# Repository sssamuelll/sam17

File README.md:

<h1 align="center">SAM17</h1>

<p align="center"><strong>A 16-voice analog synthesizer that patches like a modular and recalls like a polysynth.</strong></p>

<p align="center">
  16 complete analog voices &nbsp;·&nbsp; FM matrix 16×16 &nbsp;·&nbsp; 8-in/8-out patch bay &nbsp;·&nbsp; STM32N657 brain running Rust &nbsp;·&nbsp; three rows on Eurorack rails<br>
  hardware CERN-OHL-S v2 &nbsp;·&nbsp; firmware GPL-3.0-or-later &nbsp;·&nbsp; documentation CC BY-SA 4.0
</p>

<p align="center">
  <a href="docs/superpowers/specs">Specs</a> &nbsp;·&nbsp;
  <a href="hardware">Hardware</a> &nbsp;·&nbsp;
  <a href="software/nucleo">Firmware</a> &nbsp;·&nbsp;
  <a href="case">Case</a> &nbsp;·&nbsp;
  <a href="https://github.com/sssamuelll/sam17/milestones">Milestones</a>
</p>

> [!IMPORTANT]
> **There is no finished unit yet.** The render above is the console as it
> stands in the OpenSCAD model in [`case/`](case); nothing in it exists yet.
> What exists physically today, of this design, is the STM32N657 evaluation
> board on the bench, with the firmware running on it. The voice board is
> specified but not yet drawn. The power supply board is routed and its parts
> are signed, but it is not yet cleared for fabrication. The first complete
> instrument is due in May 2027. Details, with dates, under
> [Status](#status-october-2026).

It began as Samuel Ballesteros's electronic engineering thesis at Universidad
Yacambú, Venezuela, in 2020, a monophonic modular in seven modules. In 2022 the
Goethe-Institut Venezuela selected it for its programme *Pensar la Música
Electrónica en Venezuela*. Since then it has been redesigned, in Germany, as
the sixteen-voice instrument this repository describes.

The working language of the project is Spanish: specs, budgets and design
notes are written in Spanish. This README is in English because it is the
front door.

## The instrument

```mermaid
flowchart LR
  MIDI["MIDI<br/>USB and DIN"] --> C
  P["Panel and display"] --> C
  C["Brain<br/>STM32N657, Rust"] -- "J2 link (SPI)" --> V
  subgraph V["Voice module: 16 channels on one board"]
    direction LR
    O["16× SSI2130<br/>oscillators"] --> F["16× MS-20 style filter<br/>LM13700"] --> A["32× VCA<br/>SSI2164"]
    M["FM matrix 16×16"] -.-> O
    X["Crosspoint<br/>2× AD75019"] --- O
    X --- A
  end
  B["Patch bay<br/>8 inputs + 8 outputs"] --- X
  A --> S["Stereo output"]
```

*Inside the instrument the patch is a preset; outside, it is a cable.*

- Sixteen complete voices, each one oscillator → filter → VCA soldered end to
  end on the same board. The copper builds channels; **the preset assigns the
  roles**: sixteen clean voices, eight FM voices with carrier and modulator, or
  any mix.
- Sixteen rather than eight because in FM each voice needs two oscillators:
  the modulator has to track its carrier in frequency. One modulator shared by
  eight different notes gives dissonant bells.
- The oscillators are SSI2130, with saw, triangle, pulse, and sine from the
  chip's shaper. A 16-line FM matrix lets any oscillator modulate any other,
  which is why all sixteen sit in one module. Split in two, the matrix splits
  with them.
- One filter per voice, a 24 dB/oct MS-20 style low-pass on an LM13700 and a
  TL074. The resonance is controlled by a VCA, never by a digipot.
- Two VCAs per voice, signal and resonance. Thirty-two in all, on eight
  SSI2164.
- The envelopes run as code on the voice module's microcontroller, with their
  own knobs on the panel. There is no envelope circuit.
- The patch bay has eight inputs and eight outputs, with jack sensing and an
  LED per jack, routed through two AD75019, a 16×16 crosspoint. The brain sends
  the crosspoint image over the J2 link.
- The brain is an STM32N657 running bare-metal Rust
  ([`software/nucleo`](software/nucleo)). It takes MIDI over USB and DIN,
  drives the panel and the display, and talks to the voice module over the J2,
  an SPI link with its header, master and recovery already specified.
- The output is stereo, with a place for each voice in the stereo field.
- The console has three rows on 104 HP Eurorack rails. The instrument's
  unified panel is on top, 3U. A slim 55 mm utility row in the middle takes the
  instrument's connection tiles; it is not Intellijel 1U and is not advertised
  as compatible. A 3U Eurorack row below is for the instrument's own expansion
  modules, with its own current budget. The skeleton is machined aluminium.
  Each side is a louvre of black anodised aluminium, 44 vertical bars the
  instrument breathes through; the rear panel is amber, and the case stands
  on a 3 mm sheet-metal base. Dimensions, materials and drawings in
  [`case/README.md`](case/README.md).
- Power is 230 VAC through an external 24 V brick, an SL Power TE90 that
  plugs into a 4-pin mini-DIN socket on the case. In the v5 supply, signed
  on 8 September 2026 ([spec](docs/superpowers/specs/2026-09-05-fuente-v5-ladrillo-design.md)),
  the AC-DC stage moves out of the case. Inside it stay five isolated DC-DC
  modules and the cascade of linear regulators carried over from v4, behind a
  protection chain against reverse polarity, overvoltage and overload. The v5
  board is routed on four layers with a clean DRC
  ([`hardware/01-power-supply/v5/fab`](hardware/01-power-supply/v5/fab)), and
  its [parts](docs/superpowers/specs/2026-10-22-fuente-v5-piezas-propuesta.md)
  were reviewed on 25 October and signed on 26 and 27 October
  ([review](docs/superpowers/specs/2026-10-25-junta-fuente-v5-piezas.md)). It
  is not cleared for copper yet: the open questions in §9.2 of the spec, 13 of
  the original 16 after Advanced Energy's first reply on 28 October, are the
  condition for fabrication, several of them answered only by the
  manufacturers. Ten hold up the board, and three only the rear panel, the
  chassis and the display. Tests that need the built board run in its
  bring-up. The test kit runs from a bench supply.

*At night, with a light inside for the render. Each side is a louvre of 44
bars, and it is where the instrument breathes.*

## Status, October 2026

The project map is the
[GitHub milestones](https://github.com/sssamuelll/sam17/milestones):
eight stages, each with its "done when" in the description, and every issue
hangs from one of them. As of 30 October 2026:

| Milestone | Done when | Where it stands |
|---|---|---|
| 1 · Power supply v4: paper closed | No open decision is left in the power supply paper | The supply that gets built is now v5, signed on 8 September. Its parts were signed on 26 and 27 October and the board regenerated with them; its gates and DRC pass. Advanced Energy answered the first round of questions on 28 October (closing `H-V2-AISLAMIENTO`); between the board and copper stand 10 open questions of §9.2 (plus 3 outside the board), the follow-ups with Advanced Energy and TRACO Power, and three open issues. The bench tests come after, on the first board |
| 2 · Power supply v4 in copper | The supply boards are built and measured on the bench | Not started. The v5 bring-up is written as a checked sheet of 109 measurements with their limits ([`check_bringup.py`](hardware/01-power-supply/v5/check_bringup.py)) |
| 3 · The brain boots | Our firmware runs on the N657, speaks USB MIDI and lights the display | In progress: the firmware has run on the NUCLEO-N657X0-Q since 1 October. It takes USB MIDI, measured at 5,000 messages per second on 19 October, and drives the J2 link from an 8 kHz tick. After a 24-hour run at 1 kHz on 17 October, the 8 kHz soak from a Raspberry Pi finished 144 hours on 27 October (4,147,199,999 transfers with zero missed deadlines, zero late EOTs and zero bad edges, covering the 8-hour horizon) |
| 4 · Test kit: brain plus one voice | A MIDI note comes in and one voice sounds through the J2 | The current front: the J2 header and master are on paper and in the firmware, which since 20 October also carries the voice module's v1 message set. The full voice board has no KiCad in the repository yet |
| 5 · The remaining boards | The rest of the boards are in KiCad with their gates green | Pending |
| 6 · Case and panel to the workshop | Case and panel cut and assembled, with the supply inside and breathing | Skeleton drawings in [`case/plans`](case/plans). The finish was decided on 11 and 12 October: louvred sides, amber rear, sheet-metal base. Next come a sample strip of the louvre and a bench test of the 24 V socket before its floor bracket goes out for quotes ([`case/RFQ.md`](case/RFQ.md)) |
| 7 · The first SAM17 that sounds | Everything in the case, calibrated, thirty minutes without drifting | Depends on all of the above |
| 8 · Parked: does not block sound | App and plugin, sequencer, the agent | Resumes after 7 |

What exists physically today, of this design, is the N657 evaluation board on
the bench.

## Where it comes from

- [`docs/thesis.pdf`](docs/thesis.pdf): the 2020 thesis, in Spanish. Seven
  monophonic modules with three CEM3340, an MS-20 style filter, and MIDI/CV
  control from a Raspberry Pi and an AD5686R DAC. Summary in
  [`docs/summary.md`](docs/summary.md), monophonic architecture in
  [`docs/architecture.md`](docs/architecture.md).
- The v1 firmware, Python on a Raspberry Pi, stays in
  [`software/midi-cv`](software/midi-cv) for reference. It is superseded.
- The thesis numbering of seven modules survives as the folder index in
  [`hardware/`](hardware), although the current design is no longer seven
  boards: the voice module absorbed four of them, for the reason given in §1
  of the [voice module spec](docs/superpowers/specs/2026-08-23-modulo-voz-total-design.md).

## Repository map

```
sam17/
├── docs/
│   ├── superpowers/specs/   The current design: dated specs, the newest one rules.
│   ├── superpowers/plans/   Work plans, one per spec.
│   ├── modules/             Documentation per thesis module.
│   ├── reference/           Datasheets and references.
│   ├── thesis.pdf           The 2020 thesis; its summary in summary.md.
│   └── architecture*.md     Monophonic (thesis), polyphonic and compute architecture.
├── hardware/
│   ├── 01-power-supply/     Power supply: v1 to v5, bring-up and budgets; v5 is the one built.
│   ├── 02-midi-cv/          The brain: the N657 board and the J2 budgets.
│   ├── 03-vco/              The voice: 16 channels, FM matrix and patch bay (its 4-VCO v1, superseded).
│   ├── 04..07/              Mixer, VCF, ADSR and VCA from the thesis, dissolved into the voice.
│   ├── bus-board/           ±12 V distribution and the ground budget.
│   └── tools/               gates.py and the check_* and *_budget scripts that are the quality gates.
├── software/
│   ├── nucleo/              Rust firmware for the STM32N657.
│   └── midi-cv/             Python firmware of v1, superseded.
├── simulations/             SPICE per block: vco, vcf, vca, adsr, mixer, power.
├── case/                    The console: cad/ (OpenSCAD), plans/ (DXF), panels/, renders/,
│                            clearance_budget.py and the workshop PLIEGO.
├── .specify/memory/         The project constitution.
└── .githooks/               The gates that run on every push.
```

## Getting started

1. **The current design lives in the dated specs** in
   [`docs/superpowers/specs/`](docs/superpowers/specs), and the newest one
   rules. The ones governing the instrument today:
   [the voice module](docs/superpowers/specs/2026-08-23-modulo-voz-total-design.md),
   [the brain v2](docs/superpowers/specs/2026-08-21-modulo-2-v2-cerebro-design.md),
   [the whole instrument](docs/superpowers/specs/2026-09-03-instrumento-entero-design.md),
   [the power supply v5](docs/superpowers/specs/2026-09-05-fuente-v5-ladrillo-design.md),
   and for the link between brain and voice the J2
   [header](docs/superpowers/specs/2026-09-02-cabecera-j2-design.md) and
   [master](docs/superpowers/specs/2026-09-03-maestro-j2-recuperacion-design.md).
   [`docs/architecture-poly.md`](docs/architecture-poly.md) is pending a
   rewrite against them and carries a notice.
2. **The hardware quality gates** run on the Python standard library, with no
   dependencies:

   ```bash
   python hardware/tools/gates.py
   ```

   It runs every `check_*.py`, every `*_budget.py`, the simulations and the
   connectivity signature. Details in
   [`hardware/tools/README.md`](hardware/tools/README.md).
3. **The firmware:**

   ```bash
   cd software/nucleo && cargo test --workspace
   ```

   The N657 binary links separately, in `software/nucleo/fw`.
4. **The console** is regenerated from [`case/`](case): its README explains
   the OpenSCAD, the DXF and the clearance budgets.
5. **To contribute**, read the [constitution](.specify/memory/constitution.md)
   and [`CONTRIBUTING.md`](CONTRIBUTING.md). Every issue carries a milestone.

## Licence and name

See [`LICENSE`](LICENSE). Hardware designs are licensed under CERN-OHL-S v2,
software under GPL-3.0-or-later, and documentation under CC BY-SA 4.0. The
original thesis is included for documentation only.

The name **SAM17** is not part of any of the licences: you may build, modify
and sell derivatives of this design under their terms, but you may not call
them SAM17 or present them as original or endorsed units. Descriptive use
("based on the SAM17 design") is fine.

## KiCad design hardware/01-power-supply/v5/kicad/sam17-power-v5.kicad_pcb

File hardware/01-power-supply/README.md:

# Hardware — Módulo 1: Alimentación

> Documentación funcional: [`docs/modules/01-power-supply.md`](../../docs/modules/01-power-supply.md).

> **Estado (2026-10-30): la fuente que se construye es la v5.** Esta carpeta
> raíz es la v1, y todo lo que sigue debajo del banner la describe a ella.
>
> | Versión | Qué es | Estado |
> |---|---|---|
> | v1 (esta carpeta) | trafo de 12 VAC y 7805/7812/7912 | no se construye (2026-08-17); `notes/design-notes.md` es la base de la que heredan las demás |
> | [v2](v2/) | la primera cascada: pre-reguladores y LT3045/LT3094 | gerbers, BOM y CPL generados, nunca se pidió |
> | [v3](v3/) | toroide y cascada lineal | no se pide (2026-09-04); su cascada sigue valiendo |
> | [v4](v4/) | seis Mean Well IRM dentro de la caja, con la cascada | superada por la v5; sus curvas y puertas son la referencia de la cascada |
> | [v5](v5/) | ladrillo externo de 24 V; dentro, la conversión DC-DC y la cascada | D-V1..D-V5 firmadas el 2026-09-08 ([spec](../../docs/superpowers/specs/2026-09-05-fuente-v5-ladrillo-design.md)) |
>
> La placa de la v5 está ruteada en 4 capas con el DRC en cero
> ([`v5/fab/`](v5/fab/README.md)) y sus
> [piezas](../../docs/superpowers/specs/2026-10-22-fuente-v5-piezas-propuesta.md)
> quedaron firmadas el 26 y 27 de octubre
> ([junta](../../docs/superpowers/specs/2026-10-25-junta-fuente-v5-piezas.md)).
> Todavía no autoriza cobre: de los 16 HUECOS de su §9.2 quedan 13 abiertos tras
> la primera respuesta de Advanced Energy del 28 de octubre (10 bloquean la
> placa y 3 solo el panel trasero, el chasis y la pantalla). El bring-up es la
> hoja de 109 puntos de [`v5/check_bringup.py`](v5/check_bringup.py).

## Resumen

Convierte 12 VAC del transformador externo en **+5 V**, **+12 V** y **−12 V**
regulados que distribuye al resto del sintetizador a través del bus interno.

> **Variante Europa (230 VAC / 50 Hz).** La tesis original (§1 de
> [`notes/design-notes.md`](notes/design-notes.md)) asume la red eléctrica de
> Venezuela (110 VAC / 60 Hz); esta build cambia el objetivo a mains europeo
> — ver [`notes/design-notes.md` §12](notes/design-notes.md#12-variante-europa-230-vac--50-hz)
> para qué cambió (MOV, fusible, transformador) y qué se mantuvo igual (NTC,
> verificado contra datasheet).

## Componentes principales

| Función | Componente |
|---------|------------|
| Rectificación | Puente de diodos (4 × 1N4007 o equivalente) |
| Regulador +5 V | LM7805 |
| Regulador +12 V | LM7812 |
| Regulador −12 V | LM7912 |
| Filtrado | Electrolíticos 4700 µF / 25 V + cerámicos 100 nF |

## Estructura del directorio

```
01-power-supply/
├── README.md
├── bom.csv
├── kicad/
│   ├── build_schematic.py   Genera sam17-power.kicad_sch (ver hardware/tools/README.md)
│   ├── check_bom.py         Cruza bom.csv contra los designadores del esquemático
│   ├── build_pcb.py         Genera sam17-power.kicad_pcb — usa pcbnew DIRECTO,
│   │                        va con el Python de KiCad, no con el del sistema
│   ├── sam17.pretty/        Huellas propias: varistor D20, NTC de disco, faston (§14.3)
│   ├── fp-lib-table         Registra sam17.pretty en el proyecto
│   ├── sam17-power.kicad_sch
│   └── sam17-power.kicad_pcb
├── schematics/
│   └── sam17-power.{svg,pdf}
├── pcb/        sam17-power-{top,bottom}.svg y .pdf
├── fab/        Gerbers + taladros, con la nota para el fabricante
└── notes/
    └── design-notes.md   Presupuesto de corriente, topología, cálculo
                          térmico y checklist de bring-up.
```

## Estado

- [x] Nota de diseño con presupuesto de corriente y cálculo térmico ([`notes/design-notes.md`](notes/design-notes.md))
- [x] Decisiones arquitectónicas resueltas (+5 V incluido, NTC soft-start, MOV en primario)
- [x] Esquemático en KiCad — rieles **±12 V y +5 V aux** (rectificación,
      7812/7912/7805, protecciones DC, indicadores), lado primario
      **230 V/50 Hz** (fusible 250 mA + MOV S20K275 + NTC de soft-start,
      [`notes/design-notes.md`](notes/design-notes.md) §10/§12) y **tierra de
      protección** con puente de chasis en punto único (§13). ERC sin errores
      ni avisos, netlist verificado, y `bom.csv` cuadra con el esquemático
      designador a designador (`python kicad/check_bom.py`).
- [x] **Salida de +5 V** — resuelto en issue #8 (opción C): el riel sale por
      `J6`, un conector de 2 posiciones aparte del bus, con retorno dedicado
      al punto de estrella (ver abajo)
- [x] **Huellas asignadas** — los 33 componentes con footprint, verificado
      contra disco en cada build. Tres huellas propias en `kicad/sam17.pretty`
      porque KiCad no las trae ([§14.3](notes/design-notes.md))
- [x] **PCB ruteada a 650 mA/riel** — 150 × 200 mm, dos capas, una sola vía,
      sin plano de masa: GND es un árbol con cero bucles verificado por
      union-find, y el retorno del +5 V llega a la estrella sin tocar ninguna
      otra rama. Franja de red horizontal arriba, aislada por ranura fresada
      (**9.43 mm medidos**), y los tres carriles en columnas, cada uno encima de
      su regulador. DRC de KiCad **0 infracciones, 0 pads sin conectar, 0
      errores de huella** ([§16](notes/design-notes.md)). Renders en
      [`pcb/`](pcb/)
- [x] **Ficheros de fabricación** — gerbers y taladros en [`fab/`](fab/), con la
      especificación de la ranura y el aviso de `BR1`
- [x] **Orden de patillas de `BR1` verificado** contra datasheet primario
      (HY Electronic DB201–DB207 Rev. 11): la pieza queda fijada en **DB207**
      y el pinout ruteado ya era el correcto — el KBP206 original era SIP y no
      encajaba en la huella ([§14.6](notes/design-notes.md), issue #11). Al
      montar: esquina `+` del cuerpo a la cruz `+` del silk
- [x] **Margen de dropout simulado** ([§15](notes/design-notes.md),
      [`simulations/power/`](../../simulations/power)) — a red nominal sobra;
      a 207 V y plena carga de diseño hace falta un transformador con
      regulación ≥ 10.7 %, que ahora el BOM pide explícitamente
- [ ] **Antes de soldar `U2`**: su tab está a VRAW− (hasta −20 V), no a masa.
      Mica y casquillo aislante obligatorios ([§16.7](notes/design-notes.md))
- [x] **Zumbido: qué radia y dónde va el transformador** ([§18](notes/design-notes.md)).
      El lazo de carga del rectificador está **medido sobre la placa ruteada**
      ([`simulations/power/hum_loop.py`](../../simulations/power/hum_loop.py)):
      cota de 6.81 cm², que a 150 mm induce 5.0 µV en un lazo víctima de 10 cm²
      contra un suelo de 7.75 µV. Pero el que manda no es ni ese lazo ni el
      núcleo: es **el mazo del secundario**, que sin trenzar son ~40 cm² y ~29 µV.
      Trenzarlo es la mejora más grande y cuesta cero
- [ ] Verificación de tensiones bajo carga (medida sobre placa real). Lo primero
      a medir es el **valle del rizado de VRAW+** en `TP1`: es el número del que
      depende todo el diseño y su margen es de +0.53 V
- [ ] Medición de rizado en cada riel
- [ ] Procedimiento de bring-up documentado

## Decisiones clave (ver [`notes/design-notes.md`](notes/design-notes.md))

- **Arquitectura**: *Opción A* — transformador 12 VAC/2 A para los rieles
  ±12 V **y +5 V** del módulo + adaptador USB 5 V independiente para el
  Raspberry Pi (evita contaminación del plano analógico con el ruido del Pi).
- **Riel +5 V incluido**: alimenta AD5686R (DAC del MIDI/CV) y LCD 16×2.
  ~150 mA con backlight; el Pi sigue alimentado aparte.
- **Reguladores**: LM7805 + LM7812 + LM7912 en TO-220 con disipador
  estándar (Tj < 70 °C en el peor caso).
- **Protección AC** (variante Europa): fusible **250 mA** lento + **MOV
  S20K275** (275 VAC, sobretensión transitoria de red) + **NTC SL10-5R020**
  (limitador de inrush al arranque, mismo componente que la variante
  110 V — rated 265 VAC, sirve igual). Valores originales de 110 V
  (500 mA / V150LA20A) documentados en design-notes.md §10 como referencia
  histórica.
- **Protección DC**: diodos anti-backfeed (1N4001) en salida de cada
  regulador + LEDs indicadores por riel.
- **Tierra de protección** ([§13](notes/design-notes.md)): puente **duro** entre
  chasis y GND, en un **punto único** (espárrago M4 dedicado). No se usa red de
  *ground lift* porque los paneles son lámina galvanizada y los ~40 jacks de
  3.5 mm ya unen chasis y GND por el casquillo — una red de lift estaría
  cortocircuitada 40 veces. El PE **no lleva pista en la PCB**: va del bornero
  `J3.3` al espárrago por cable, y el 0 V sube al mismo espárrago por el faston
  `J5`. La corriente de falla nunca pasa por la placa.
- **Interfaz del bus** ([§10.4](notes/design-notes.md), issue #8): `J2` lleva
  solo lo analógico (`+12/GND/GND/−12`, igual para los módulos 2-7) y el +5 V
  sale por `J6`, un conector de 2 posiciones físicamente distinto. Así ningún
  módulo recibe un +5 V que no usa, el feed digital no se puede cruzar con
  ±12, y el retorno del +5 V — que §10.1 exige dedicado hasta el punto de
  estrella porque el backlight del LCD va conmutado — queda separado por
  construcción, no por convención de layout.
- **Distribución**: bus board PCB (no daisy-chain) con tierra en estrella
  desde los condensadores bulk.

## Cruce esquemático ↔ BOM

`bom.csv` lleva ahora una columna `refs` con los designadores reales del
esquemático, y `kicad/check_bom.py` verifica el cruce en los dos sentidos. Hoy
cuadra: 32 componentes en la hoja, ninguno sin línea de compra, ninguna línea
apuntando a un designador que no existe.

Resuelto en esa pasada, además de los dos huecos que la motivaron:

- **`J1` de 3 posiciones, no 2.** El secundario es de toma central: son tres
  hilos (12 VAC / CT / 12 VAC). El esquemático tenía razón y el BOM estaba
  viejo.
- **`R3` es de 680 Ω, no de 2.2 kΩ.** El BOM pedía tres resistencias iguales
  para los tres LED. A 5 V, 2.2 kΩ dan ~1.3 mA y el indicador de +5 V queda
  apagado; 680 Ω dan los mismos ~4.5 mA que los otros dos rieles.
- **Designadores alineados.** El BOM llamaba `MOV1`/`NTC1` a lo que la hoja
  llama `RV1`/`NT1`, y sus `C3`/`C4`/`C5` eran condensadores distintos de los
  `C3`/`C4`/`C5` del esquemático. Eso hacía el cruce imposible de automatizar.
- **Faltaban `J4` y `J5`** en la lista de compra.

## Resuelto: la salida de +5 V y la interfaz del bus (issue #8)

El riel de +5 V no salía de la placa (netlist sin ningún pin de `J2` en la red
`+5V`), y arreglarlo era fijar la **interfaz del bus** de la que dependen los
módulos 2-7. Se decidió la **opción C** del issue:

- `J2` intacto — `+12 / GND / GND / −12`, el mismo bus analógico para todos.
- `J6` nuevo — 2 posiciones, solo el feed de +5 V al módulo 2. Netlist ahora:
  `+5V: C10/1, C11/1, D5/2, J6/1, R3/1, U3/3`.

El porqué (contra el header 2×5 que pedía el BOM viejo) está en
[`notes/design-notes.md` §10.4](notes/design-notes.md): retorno del +5 V
dedicado por construcción (§10.1, el backlight va conmutado), ningún +5 V vivo
en módulos que no lo usan, y la tesis nunca tuvo un bus formal que respetar.
Las líneas de `J2` y `J6` en `bom.csv` vuelven a ser comprables.

## Mejoras propuestas

Ver la sección *Mejoras propuestas* en
[`docs/modules/01-power-supply.md`](../../docs/modules/01-power-supply.md).

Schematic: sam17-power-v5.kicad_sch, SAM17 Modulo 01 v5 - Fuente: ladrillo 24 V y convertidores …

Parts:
C1, C2: 220uF 35V; CP_Elec_8x10; MPN EEEFK1V221P; LCSC C178562
C3, C4, C17, C18: 47uF 35V; CP_Elec_6.3x7.7; MPN VZH470M1VTR-0607; LCSC C249923
C5, C6, C9, C23, C24, C25, C26, C27, C28, C30, C31, C32, C33, C34, C35: 100nF 50V X7R; C_0805_2012Metric; MPN CC0805KRX7R9BB104; LCSC C49678
C7: 1uF 50V X7R; C_0805_2012Metric; MPN CL21B105KBFNNNE; LCSC C28323
C8: 4.7uF 25V X7R; C_0805_2012Metric; MPN CC0805KKX7R8BB475; LCSC C354262
C10: 100nF 100V X7R; C_0805_2012Metric; MPN CC0805KKX7R0BB104; LCSC C106243
C11, C13: 22nF 50V X7R; C_0805_2012Metric; MPN CL21B223KBANNNC; LCSC C1729
C12: 1nF 50V C0G; C_0805_2012Metric; MPN CC0805JRNPO9BN102; LCSC C62774
C14: 100uF 50V; CP_Elec_8x10; MPN EEEFK1H101P; LCSC C178548
C16, C20, C22, C36, C37, C38: 22uF 25V X7R; C_1210_3225Metric; MPN GRM32ER71E226KE15L; LCSC C21397
C19, C21: 470nF 50V X7R; C_0805_2012Metric; MPN CL21B474KBFNNNE; LCSC C13967
C29: 100uF 25V; CP_Elec_6.3x7.7; MPN UCD1E101MCL1GS; LCSC C250945
C39: 1000uF 16V; CP_Elec_10x10; MPN VZH102M1CTR-1010; LCSC C249844
D1: SMBJ33CA; D_SMB; MPN SMBJ33CA; LCSC C83325
D2: BZT52C24; D_SOD-123; MPN BZT52C24-7-F; LCSC C171749
D3: LED rojo 3mm; LED_D3.0mm; MPN 204-10SURD/S530-A3-L; LCSC C99771
D4: LED amarillo 3mm; LED_D3.0mm; MPN 204-10UYD/S530-A3-L; LCSC C85160
D6: LED verde 3mm; LED_D3.0mm; MPN 204-10SYGD/S530-E2-L; LCSC C181864
D7: LED azul 3mm; LED_D3.0mm; MPN 204-10SUBC/S400-A4; LCSC C86881
D10: SMBJ16A; D_SMB; MPN SMBJ16A; LCSC C151254
D11: BAT54WS; D_SOD-323; MPN BAT54WS-7-F; LCSC C124205
D12, D13: S1M; D_SMA; MPN S1M-E3/61T; LCSC C144860
D14, D15, D16, D17: BAT54S; SOT-23; MPN BAT54SLT1G; LCSC C19726
D18: LED verde 0805; LED_0805_2012Metric; MPN LTST-C170KGKT; LCSC C98221
D19: SS34; D_SMA; MPN SS34; LCSC C8678
D20: BZT52C15; D_SOD-123; MPN BZT52C15-7-F; LCSC C177014
F2, F3: SF-1206F300-2 3A; Fuse_1206_3216Metric; MPN SF-1206F300-2; LCSC C208499
F4: SF-1206F200-2 2A; Fuse_1206_3216Metric; MPN SF-1206F200-2; LCSC C719183
F5: 0466004 4A; Fuse_1206_3216Metric; MPN 0466004.NRHF; LCSC C187596
FB1, FB2: BLM21PG600SN1D; L_0805_2012Metric; MPN BLM21PG600SN1D; LCSC C18305
J1: Bornera 2P 5.0 mm; TerminalBlock_MaiXu_MX126-5.0-02P_1x02_P5.00mm; MPN MX126-5.0-02P-GN01-Cu-S-A; LCSC C5188434
J2, J7: Molex KK-254 4P; Molex_KK-254_AE-6410-04A_1x04_P2.54mm_Vertical; MPN 22-27-2041; LCSC C504991
J3: Bornera 4P 5.08 mm; TerminalBlock_Phoenix_MKDS-1,5-4-5.08_1x04_P5.08mm_Horizont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; MPN 1715747; LCSC C5443561
J5: Faston 6.3x0.8 PCB; Faston_6.3x0.8mm_PCB_2Leg_P5.0mm; MPN 3866A.68
J6, J9: Molex KK-254 2P; Molex_KK-254_AE-6410-02A_1x02_P2.54mm_Vertical; MPN 22-27-2021; LCSC C293316
J8, J10: PinHeader 1x04; PinHeader_1x04_P2.54mm_Vertical; MPN PZ254V-11-04P; LCSC C2691448
L2, L3: 22uH SRP1265A-220M; L_Bourns_SRP1265A; MPN SRP1265A-220M; LCSC C2041465
NT1: NetTie GND24-GNDA; NetTie-2_SMD_Pad2.0mm; MPN —
PS1: THN 30-2422WI; Converter_DCDC_TRACO_THL30-xxxxWI_THT; MPN THN 30-2422WI
PS2: URB2405YMD-20WR3; Converter_DCDC_Mornsun_URB_YMD-20WR3_Horizontal_THT; MPN URB2405YMD-20WR3
PS3: THN 20-2411WI; Converter_DCDC_TRACO_THL30-xxxxWI_THT; MPN THN 20-2411WI
PS4, PS5: THN 20-2413WI; Converter_DCDC_TRACO_THL30-xxxxWI_THT; MPN THN 20-2413WI
Q2, Q7: CSD18534Q5A; TDSON-8-1; MPN CSD18534Q5A; LCSC C115943
Q3, Q4, Q5, Q6: MMBT3906; SOT-23; MPN MMBT3906LT1G; LCSC C53444
R1, R2, R57, R58, R59, R60: 2.2k; R_0805_2012Metric; MPN 0805W8F2201T5E; LCSC C17520
R3, R4: 680; R_0805_2012Metric; MPN 0805W8F6800T5E; LCSC C17798
R5: 9.31k 0.1%; R_0805_2012Metric; MPN RT0805BRD079K31L; LCSC C865720
R6, R8: 1.00k 0.1%; R_0805_2012Metric; MPN RT0805BRD071KL; LCSC C110774
R7: 9.09k 0.1%; R_0805_2012Metric; MPN RT0805BRD079K09L; LCSC C865717
R9, R10, R61, R62: 120k 0.1%; R_0805_2012Metric; MPN RT0805BRD07120KL; LCSC C865161
R11: 4.02k; R_0805_2012Metric; MPN 0805W8F4021T5E; LCSC C17663
R12, R35: 49.9k 0.1%; R_0805_2012Metric; MPN RT0805BRD0749K9L; LCSC C469661
R13: 1.62k 0.1%; R_0805_2012Metric; MPN TC0525B1621T5G; LCSC C50670348
R14: 1.96k 0.1%; R_0805_2012Metric; MPN TNPW08051K96BEEN; LCSC C2093012
R15, R16, R17, R18, R19, R29, R30: 0.02; R_2512_6332Metric; MPN WSL2512R0200FEA; LCSC C553969
R20: 0.1; R_2512_6332Metric; MPN WSL2512R1000FEA; LCSC C844904
R21, R22, R23, R24: 100k 0.1%; R_0805_2012Metric; MPN RT0805BRD07100KL; LCSC C122537
R25, R26, R27, R28: 20.0k 0.1%; R_0805_2012Metric; MPN RT0805BRD0720KL; LCSC C469660
R31: 220; R_0805_2012Metric; MPN 0805W8F2200T5E; LCSC C17557
R32, R33, R45, R46: 45.3k 0.1%; R_0805_2012Metric; MPN RT0805BRE0745K3L; LCSC C866072
R34: 18.2k; R_0805_2012Metric; MPN 0805W8F1822T5E; LCSC C17497
R36: 3.74k 0.1%; R_0805_2012Metric; MPN RT0805BRD073K74L; LCSC C865467
R37, R38: 0.68; R_1206_3216Metric; MPN 1206W4F680LT5E; LCSC C19108
R39: 47.5k 0.1%; R_0805_2012Metric; MPN RT0805BRD0747K5L; LCSC C865514
R40, R47, R48, R50, R52: 10.0k 0.1%; R_0805_2012Metric; MPN RT0805BRD0710KL; LCSC C110775
R41: 10.2k 0.1%; R_0805_2012Metric; MPN RT0805BRD0710K2L; LCSC C865134
R42: 59.0k 0.1%; R_0805_2012Metric; MPN RT0805BRD0759KL; LCSC C865570
R43: 100k; R_0805_2012Metric; MPN 0805W8F1003T5E; LCSC C149504
R44, R66, R68, R74, R75, R76, R77, R84, R85: 10k; R_0805_2012Metric; MPN 0805W8F1002T5E; LCSC C17414
R49, R51: 12.7k 0.1%; R_0805_2012Metric; MPN TC0525B1272T5G; LCSC C50670219
R53, R54, R55, R56, R78, R79, R80, R81: 100; R_0805_2012Metric; MPN 0805W8F1000T5E; LCSC C17408
R63, R64: 1.2k; R_0805_2012Metric; MPN 0805W8F1201T5E; LCSC C17379
R65, R83: 47k; R_0805_2012Metric; MPN 0805W8F4702T5E; LCSC C17713
R67, R82: 6.8M; R_0805_2012Metric; MPN 0805W8F6804T5E; LCSC C17773
R69: 10M; R_0805_2012Metric; MPN 0805W8F1005T5E; LCSC C26108
R70, R71, R72, R73: 1k; R_0805_2012Metric; MPN 0805W8F1001T5E; LCSC C17513
RV2, RV3: 1k 3296W; Potentiometer_Bourns_3296W_Vertical; MPN 3296W-1-102LF; LCSC C57089
SCR1, SCR2, SCR3, SCR4: BT151-500R; TO-220-3_Vertical; MPN BT151-500R,127; LCSC C9211
SW1: Pulsador 6x6; SW_PUSH_6mm; MPN B3F-1000; LCSC C93157
TP1, TP2, TP3, TP4, TP5, TP6, TP7, TP8, TP9, TP10, TP11: TestPoint; TestPoint_THTPad_D2.0mm_Drill1.0mm; MPN —
U1: LT1963AEQ; TO-263-5_TabPin3; MPN LT1963AEQ#TRPBF; LCSC C459702
U2: LT3015EQ; TO-263-5_TabPin3; MPN LT3015EQ#PBF; LCSC C666306
U4, U5: LT3045EDD; DFN-10-1EP_3x3mm_P0.5mm_EP1.65x2.38mm_ThermalVias; MPN LT3045EDD#TRPBF; LCSC C514420
U6, U7: LT3094EDD; DFN-12-1EP_3x3mm_P0.45mm_EP1.65x2.38mm_ThermalVias; MPN LT3094EDD#TRPBF; LCSC C670493
U8, U12, U13, U14: INA226; TSSOP-10_3x3mm_P0.5mm; MPN INA226AIDGSR; LCSC C49851
U9: ISO1541; SOIC-8_3.9x4.9mm_P1.27mm; MPN ISO1541DR; LCSC C143028
U10: ADS1115IDGS; TSSOP-10_3x3mm_P0.5mm; MPN ADS1115IDGSR; LCSC C37593
U11: TMP1075DGK; VSSOP-8_3x3mm_P0.65mm; MPN TMP1075DGKR; LCSC C2864807
U15: LM74502DDFR; SOT-23-8; MPN LM74502DDFR; LCSC C3236215
U16, U19: TPS26631PWPR; HTSSOP-20-1EP_4.4x6.5mm_P0.65mm_EP3.4x6.5mm_Mask2.96x2.96mm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; MPN TPS26631PWPR; LCSC C2866319
U17: MSP430FR2111IPW16; TSSOP-16_4.4x5mm_P0.65mm; MPN MSP430FR2111IPW16R; LCSC C2052845
U18: TPS70933DBVR; SOT-23-5; MPN TPS70933DBVR; LCSC C89347
U20: LM393B; SOIC-8_3.9x4.9mm_P1.27mm; MPN LM393BIDR; LCSC C2865059
U21, U22, U23, U24, U25: TL431BI; SOT-23; MPN TL431BIDBZR; LCSC C41283

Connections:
+3V3_DIG: C28.1, J8.1, R59.1, R60.1, U9.8 (VCC2)
+3V3_MCU: C8.1, C23.1, J10.1, R65.1, R66.1, R84.1, U17.5 (DVCC), U18.5 (OUT)
+5V_AUX: C24.1, C25.1, C26.1, C27.1, C30.1, C31.1, C32.1, C33.1, D14.2 (K), D15.2 (K), D16.2 (K), D17.2 (K), J6.1, R20.2, R25.2, R27.2, R28.2, R44.1, R57.1, R58.1, R63.1, U8.6 (VS), U9.1 (VCC1), U10.8 (VDD), U11.7 (A0), U11.8 (V+), U12.2 (A0), U12.6 (VS), U12.8 (Vbus), U12.9 (Vin-), U13.1 (A1), U13.6 (VS), U14.1 (A1), U14.2 (A0), U14.6 (VS), U20.8 (V+)
+5V_DIG: F5.2, J9.1, Q6.2 (E), R4.1, R51.1, R77.1, SCR4.2 (A)
+5V_FUSED_RACK: F4.2, R20.1, R30.1, U12.10 (Vin+), U14.10 (Vin+)
+5V_RACK: J3.4, Q5.2 (E), R3.1, R30.2, R49.1, R76.1, SCR3.2 (A), TP5.1, U14.8 (Vbus), U14.9 (Vin-)
+5V_RAW_DIG: C29.1, F5.1, PS2.4 (+Vo)
+5V_RAW_RACK: C16.1, C39.1, F4.1, PS3.3 (+Vout)
+12V_FUSED_RACK: F2.2, R29.1, U13.10 (Vin+)
+12V_RACK: J3.1, Q3.2 (E), R29.2, R45.1, R74.1, SCR1.2 (A), U13.8 (Vbus), U13.9 (Vin-)
+12V_RAW_RACK: F2.1, PS1.3 (+Vout)
+12V_ULTRA: C20.1, J2.4, J7.4, R1.1, R19.2, TP3.1, U8.8 (Vbus), U8.9 (Vin-)
+13V1: C17.1, C36.1, D12.2 (A), R5.1, TP7.1, U1.4 (OUT), U4.1 (IN), U4.2 (IN), U4.3 (EN/UV), U4.6 (PGFB), U5.1 (IN), U5.2 (IN), U5.3 (EN/UV), U5.6 (PGFB)
+15V5_EFUSE: D19.1 (K), L2.1, U19.18 (OUT), U19.19 (OUT), U19.20 (OUT)
+15V5_FILT: D10.1 (K), D12.1 (K), FB1.2, U1.2 (IN)
+15V5_LC: C1.1, C3.1, C5.1, FB1.1, L2.2, R22.1, R39.1, TP9.1
+15V5_RAW: PS4.3 (+Vout), R35.1, R82.1, U19.1 (IN), U19.2 (IN), U19.3 (IN), U19.6 (IN_SYS)
+24V_LDO: C7.1, D2.1 (K), R64.2, U18.1 (IN)
+24V_PROT: Q2.5 (D), R12.1, R64.1, U16.1 (IN), U16.2 (IN), U16.3 (IN), U16.6 (IN_SYS)
+24V_RAW: C9.2, C10.1, D1.1 (A1), J1.1, Q2.1 (S), Q2.2 (S), Q2.3 (S), R85.1, TP1.1, U15.1 (EN/UVLO), U15.5 (VS), U15.8 (SRC)
+24V_SW: C14.1, PS1.1 (+Vin), PS2.3 (Vin), PS3.1 (+Vin), PS4.1 (+Vin), PS5.1 (+Vin), U16.18 (OUT), U16.19 (OUT), U16.20 (OUT)
-12V9: C18.2, C37.2, D13.1 (K), R7.1, TP8.1, U2.5 (OUT), U6.1 (IN), U6.2 (IN), U6.3 (EN/UV), U6.5 (PGFB), U6.13 (IN), U7.1 (IN), U7.2 (IN), U7.3 (EN/UV), U7.5 (PGFB), U7.13 (IN)
-12V_RACK: F3.2, J3.3, R24.1, R48.2, R54.2, SCR2.1 (K), U23.3 (A)
-12V_RAW_RACK: F3.1, PS1.5 (-Vout)
-12V_ULTRA: C22.2, J2.1, J7.1, R2.2, R17.2, R18.2, R21.1, TP4.1, U6.10 (OUTS), U7.10 (OUTS)
-15V5_FILT: D11.2 (A), D13.2 (A), FB2.2, U2.3 (IN)
-15V5_LC: C4.2, C6.2, FB2.1, L3.2, R23.1, R38.2, R42.2, TP10.1
-15V5_RAW: L3.1, PS5.5 (-Vout), R33.2
ADJ_U1: R6.1, RV2.2, RV2.3, U1.5 (ADJ)
ADJ_U2: R8.1, RV3.2, RV3.3, U2.4 (ADJ)
AIN0: D14.3 (COM), R21.2, R25.1, U10.4 (AIN0)
AIN1: D15.3 (COM), R22.2, R26.1, U10.5 (AIN1)
AIN2: D16.3 (COM), R23.2, R27.1, U10.6 (AIN2)
AIN3: D17.3 (COM), R24.2, R28.1, U10.7 (AIN3)
C1_NEG: C1.2, R37.1
C2_NEG: C2.2, R38.1
DVDT_U16: C11.1, U16.10 (dVdT)
DVDT_U19: C13.1, U19.10 (dVdT)
FLT_M5: R66.2, U16.15 (~FLT), U17.1 (P1.1)
FLT_U19: R84.2, U17.16 (P1.2), U19.15 (~FLT)
GATE_Q2: Q2.4 (G), U15.6 (GATE)
GATE_SCR1: R53.1, R78.2, SCR1.3 (G)
GATE_SCR2: R54.1, R79.2, SCR2.3 (G)
GATE_SCR3: R55.1, R80.2, SCR3.3 (G)
GATE_SCR4: R56.1, R81.2, SCR4.3 (G)
GND24: C7.2, C8.2, C10.2, C11.2, C12.2, C14.2, C23.2, D2.2 (A), D18.1 (K), D20.2 (A), J10.4, NT1.1, PS1.2 (-Vin), PS2.2 (GND), PS3.2 (-Vin), PS4.2 (-Vin), PS5.2 (-Vin), Q7.1 (S), Q7.2 (S), Q7.3 (S), R11.2, R14.2, R83.2, SW1.2, TP2.1, U15.2 (GND), U15.7 (OV), U16.9 (GND), U16.16 (PGTH), U16.21 (GND), U17.6 (DVSS), U18.2 (GND)
GNDA: C2.1, C3.2, C4.1, C5.2, C6.1, C13.2, C16.2, C17.2, C18.1, C19.2, C20.2, C21.2, C22.1, C24.2, C25.2, C26.2, C27.2, C30.2, C31.2, C32.2, C33.2, C34.2, C35.2, C36.2, C37.1, C38.2, C39.2, D3.1 (K), D4.2 (A), D6.1 (K), D10.2 (A), D11.1 (K), D14.1 (A), D15.1 (A), D16.1 (A), D17.1 (A), D19.2 (A), J2.2, J2.3, J3.2, J5.1, J6.2, J7.2, J7.3, NT1.2, PS1.4 (Common), PS3.5 (-Vout), PS4.5 (-Vout), PS5.3 (+Vout), Q4.2 (E), R6.2, R8.2, R9.2, R10.2, R26.2, R32.2, R34.2, R36.2, R37.2, R40.2, R43.2, R46.1, R47.2, R50.2, R53.2, R55.2, R61.2, R62.2, R68.2, R75.1, SCR1.1 (K), SCR2.2 (A), SCR3.1 (K), TP6.1, U1.3 (GND), U2.2 (GND), U4.5 (ILIM), U4.8 (GND), U4.11 (GND), U5.5 (ILIM), U5.8 (GND), U5.11 (GND), U6.6 (ILIM), U6.9 (GND), U7.6 (ILIM), U7.9 (GND), U8.1 (A1), U8.2 (A0), U8.7 (GND), U9.4 (GND1), U10.1 (ADDR), U10.3 (GND), U11.4 (GND), U11.5 (A2), U11.6 (A1), U12.1 (A1), U12.7 (GND), U13.2 (A0), U13.7 (GND), U14.7 (GND), U19.9 (GND), U19.12 (MODE), U19.16 (PGTH), U19.21 (GND), U20.4 (V-), U21.3 (A), U22.3 (A), U24.3 (A)
GNDD: C28.2, C29.2, D7.1 (K), J8.4, J9.2, PS2.6 (0V), R52.2, R56.2, SCR4.1 (K), TP11.1, U9.5 (GND2), U25.3 (A)
G_Q7: D20.1 (K), Q7.4 (G), R85.2
ILIM_U16: R11.1, U16.11 (ILIM)
ILIM_U19: R34.1, U19.11 (ILIM)
LED3_A: D3.2 (A), R1.2
LED4_K: D4.1 (K), R2.1
LED6_A: D6.2 (A), R3.2
LED7_A: D7.2 (A), R4.2
LED_ANODE: D18.2 (A), R31.2
LED_CTRL: R31.1, U17.14 (P1.4)
MCU_RST: C12.1, J10.3, R65.2, U17.4 (RST/NMI/SBWTDIO)
MCU_TEST: J10.2, U17.3 (TEST/SBWTCK)
OUTS_POS: C38.1, R15.2, R16.2, R19.1, U4.9 (OUTS), U5.9 (OUTS), U8.10 (Vin+)
OUT_U4: R15.1, U4.10 (OUT)
OUT_U5: R16.1, U5.10 (OUT)
OUT_U6: R17.1, U6.11 (OUT), U6.12 (OUT)
OUT_U7: R18.1, U7.11 (OUT), U7.12 (OUT)
OVP_U16: R13.2, R14.1, U16.8 (OVP)
OVP_U19: R35.2, R36.1, U19.8 (OVP)
QB_CB1: Q3.1 (B), R70.1, R74.2
QB_CB2: Q4.1 (B), R71.1, R75.2
QB_CB3: Q5.1 (B), R72.1, R76.2
QB_CB4: Q6.1 (B), R73.1, R77.2
QC_CB1: Q3.3 (C), R78.1
QC_CB2: Q4.3 (C), R79.1
QC_CB3: Q5.3 (C), R80.1
QC_CB4: Q6.3 (C), R81.1
REF0_NEG: R68.1, R69.2, U20.5 (+)
REF_CB1: R45.2, R47.1, U22.2 (REF)
REF_CB2: R46.2, R48.1, U23.2 (REF)
REF_CB3: R49.2, R50.1, U24.2 (REF)
REF_CB4: R51.2, R52.1, U25.2 (REF)
RET24_RAW: D1.2 (A2), J1.2, Q7.5 (D)
SCL_A: R58.2, U8.5 (SCL), U9.3 (SCL1), U10.10 (SCL), U11.2 (SCL), U12.5 (SCL), U13.5 (SCL), U14.5 (SCL)
SCL_D: J8.3, R60.2, U9.6 (SCL2)
SDA_A: R57.2, U8.4 (SDA), U9.2 (SDA1), U10.9 (SDA), U11.1 (SDA), U12.4 (SDA), U13.4 (SDA), U14.4 (SDA)
SDA_D: J8.2, R59.2, U9.7 (SDA2)
SENSE_NEG: C35.1, R41.2, R42.1, U20.6 (-)
SENSE_POS: C34.1, R39.2, R40.1, R67.2, U20.3 (+)
SET_NEG: C21.1, R10.1, R62.1, U6.8 (SET), U7.8 (SET)
SET_POS: C19.1, R9.1, R61.1, U4.7 (SET), U5.7 (SET)
SHDN_CASCADE: R43.1, R44.2, R67.1, R69.1, U1.1 (~SHDN), U2.1 (~SHDN), U20.1, U20.7
SHDN_M5: R83.1, U16.13 (~SHDN), U17.15 (P1.3)
SW_RESET: SW1.1, U17.13 (P1.5)
TLK_CB1: R70.2, U22.1 (K)
TLK_CB2: R71.2, U23.1 (K)
TLK_CB3: R72.2, U24.1 (K)
TLK_CB4: R73.2, U25.1 (K)
TRIM_PS4: PS4.4 (Trim), R32.1
TRIM_PS5: PS5.4 (Trim), R33.1
TRIM_U1_HI: R5.2, RV2.1
TRIM_U2_HI: R7.2, RV3.1
UVLO_U16: R12.2, R13.1, U16.7 (UVLO)
UVLO_U19: R82.2, U19.7 (UVLO)
VCAP_U15: C9.1, U15.4 (VCAP)
VREF_2V5: R41.1, R63.2, U20.2 (-), U21.1 (K), U21.2 (REF)

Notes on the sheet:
BLOQUE M5: Entrada 24 V, polaridad (LM74502 + 2 x CSD18534Q5A, +24 V y retorno), eFuse U16 y supervisor M5
BLOQUE DCDC: Convertidores: THN 30 (+-12 rack), URB (+5 digital M1), 3 x THN 20 (+5 rack, +-15.5)
BLOQUE LC: Tope M3 (#334): TPS26631 + filtro LC 22 uH / 47 uF / 0.68 ohm + 220 uF + SMBJ16A
BLOQUE DF4: Detector D-F4: LM393 + TL431, umbral 14.5 V con histeresis
BLOQUE PRE: Pre-reguladores LT1963A (+13.1 V) y LT3015 (-12.9 V)
BLOQUE ULTRA: Cascada ultra: 2 x LT3045 y 2 x LT3094 en paralelo, R_SET = 60k
BLOQUE DF6: Rack: fusibles y crowbars D-F6 (TL431 -> PNP -> BT151)
BLOQUE TEL: Telemetria I2C: 4 x INA226, ADS1115, TMP1075 e ISO1541
BLOQUE CON: Conectores
PWR_FLAG: redes que alimenta algo pasivo o un conector

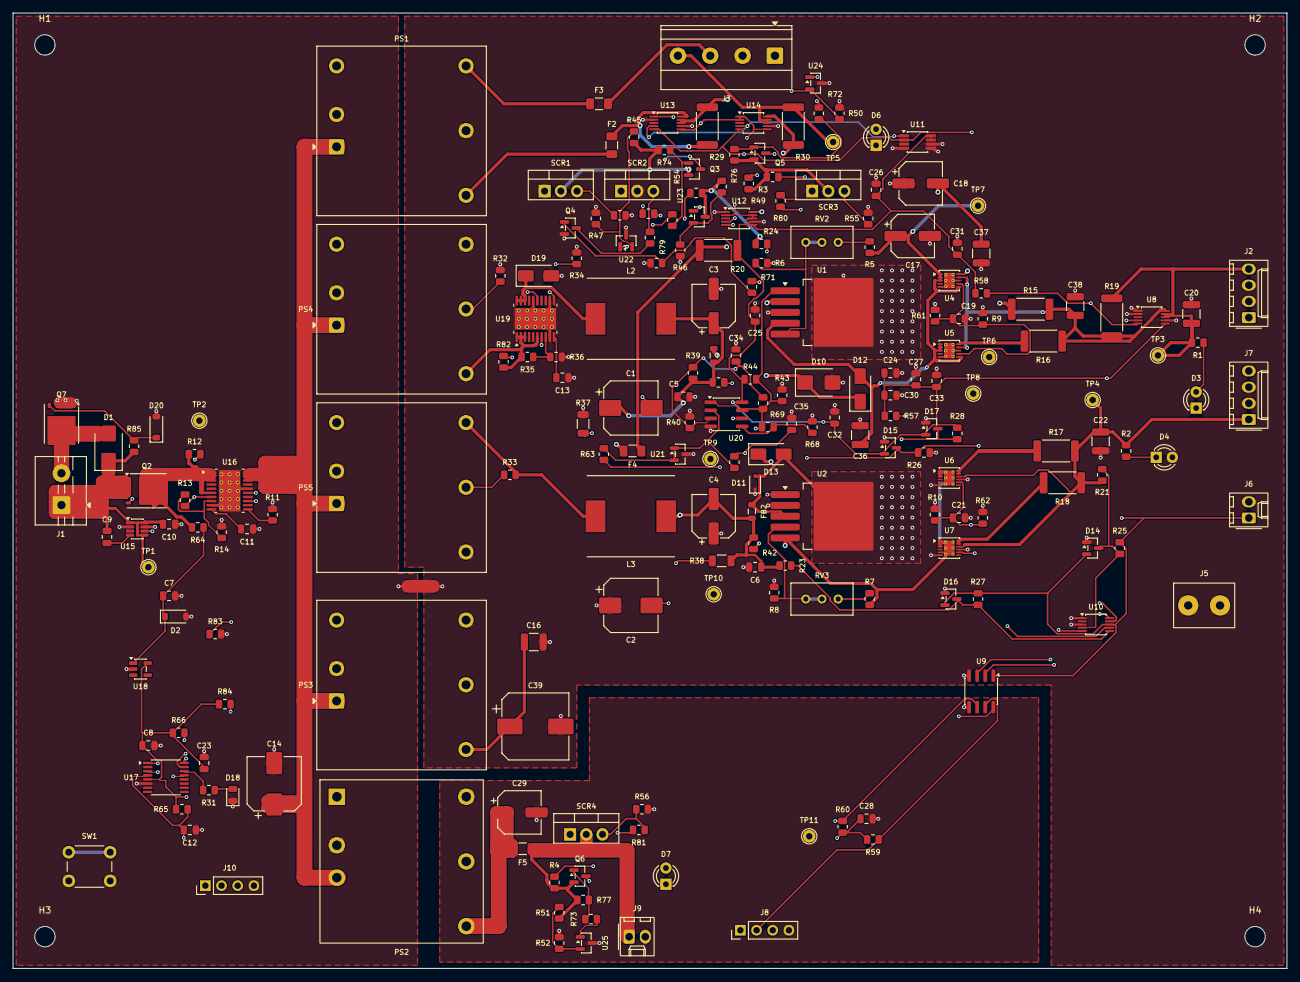
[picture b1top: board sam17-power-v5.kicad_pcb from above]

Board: 4 copper layers, 200.0 x 150.0 mm, 215 parts (0 on the bottom side), 103 nets.

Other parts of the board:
H1, H2, H3, H4: MountingHole_3.2mm_M3

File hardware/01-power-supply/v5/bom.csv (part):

refs,value,footprint,quantity,fabricante,mpn,lcsc,supplier,notes
J1,Bornera 2P 5.0 mm,TerminalBlock:TerminalBlock_MaiXu_MX126-5.0-02P_1x02_P5.00mm,1,MaiXu,MX126-5.0-02P-GN01-Cu-S-A,C5188434,LCSC,"Entrada del cableado desde el conector de panel (Kycon KPJX-PM-4S en bom-chasis.csv). 1 = +24V_RAW, 2 = RET24_RAW (GND24 detras de Q7)."
D1,SMBJ33CA,Diode_SMD:D_SMB,1,Littelfuse,SMBJ33CA,C83325,LCSC,"TVS BIDIRECCIONAL a los dos lados de J1, entre +24V_RAW y RET24_RAW: la corriente de un transitorio vuelve por J1 sin cruzar Q7. Un unidireccional conduce en directa con el ladrillo al reves (#474). V_RWM 33 V, V_BR 36.7..40.6 V a 1 mA, V_C 53.3 V a I_PP 11.3 A (bourns_smbj.pdf p. 2, valores JEDEC iguales a los que LCSC lista para C83325; la hoja de Littelfuse no esta en el repo). Su V_BR minimo queda por encima del OVP del TE90 (36.0 V max, ae-TE90-datasheet.pdf p. 2) y del de U16: no conduce con el ladrillo en OVP (check_absmax.py). Junta de piezas v5 sec. 3.8, #494."
"Q2,Q7",CSD18534Q5A,Package_TO_SOT_SMD:TDSON-8-1,2,Texas Instruments,CSD18534Q5A,C115943,LCSC,"MOSFET de proteccion de polaridad. Q2, lado positivo: FUENTE en +24V_RAW, drenador en +24V_PROT (lm74502.pdf p. 1). Q7, lado del retorno (H-V5-INVERSION): drenador en RET24_RAW (J1.2), fuente en GND24, puerta en G_Q7 desde +24V_RAW por R85 y con D20 a GND24; el diodo de cuerpo conduce en normal y el canal se enriquece, con el ladrillo al reves bloquea. VDS 60 V, VGS +-20 V (csd18534q5a.pdf p. 1), RDS(on) 9.8 mohm max a VGS 10 V y 25 C (p. 3)."
U15,LM74502DDFR,Package_TO_SOT_SMD:SOT-23-8,1,Texas Instruments,LM74502DDFR,C3236215,LCSC,Controlador de polaridad. VS = SRC = EN = +24V_RAW; OV a GND24 (el OVP lo hace U16).
"U16,U19",TPS26631PWPR,Package_SO:HTSSOP-20-1EP_4.4x6.5mm_P0.65mm_EP3.4x6.5mm_Mask2.96x2.96mm_ThermalVias,2,Texas Instruments,TPS26631PWPR,C2866319,LCSC,"eFuse 60 V con OVP ajustable. La TPS26630PWPR de #474 no existe: TI solo vende el TPS26630 en VQFN-24 (tps2663.pdf, orderables). U16: 4.5 A, MODE al aire (enclava). U19: 1.0 A, MODE a GND (reintenta)."
U18,TPS70933DBVR,Package_TO_SOT_SMD:SOT-23-5,1,Texas Instruments,TPS70933DBVR,C89347,LCSC,"LDO 3.3 V del supervisor. EN al aire (pull-up interno, EN <= 6.5 V)."
U17,MSP430FR2111IPW16,Package_SO:TSSOP-16_4.4x5mm_P0.65mm,1,Texas Instruments,MSP430FR2111IPW16R,C2052845,LCSC,"Supervisor M5. P1.1 = FLT, P1.3 = SHDN de U16, P1.4 = LED, P1.5 = boton (msp430fr2111.pdf p. 8). STOCK BAJO en LCSC (7 uds el 2026-10-22): reservar o comprar en Mouser/DigiKey."
U1,LT1963AEQ,Package_TO_SOT_SMD:TO-263-5_TabPin3,1,Analog Devices,LT1963AEQ#TRPBF,C459702,LCSC,Pre-regulador +13.10 V. AJUSTABLE: el SOT-223 de #474 solo existe en 1.5/1.8/2.5/3.3 V fijos.
U2,LT3015EQ,Package_TO_SOT_SMD:TO-263-5_TabPin3,1,Analog Devices,LT3015EQ#PBF,C666306,LCSC,Pre-regulador -12.90 V. El TAB es IN (lt3015-rev-b.pdf p. 2).
"U4,U5",LT3045EDD,Package_DFN_QFN:DFN-10-1EP_3x3mm_P0.5mm_EP1.65x2.38mm_ThermalVias,2,Analog Devices,LT3045EDD#TRPBF,C514420,LCSC,"+12 V ultra en paralelo. PGFB a IN (si no, el arranque rapido de 2 mA queda enganchado)."
"U6,U7",LT3094EDD,Package_DFN_QFN:DFN-12-1EP_3x3mm_P0.45mm_EP1.65x2.38mm_ThermalVias,2,Analog Devices,LT3094EDD#TRPBF,C670493,LCSC,-12 V ultra en paralelo. PGFB a IN y VIOC al aire (lt3094-rev-b.pdf p. 9).
"U8,U12,U13,U14",INA226,Package_SO:TSSOP-10_3x3mm_P0.5mm,4,Texas Instruments,INA226AIDGSR,C49851,LCSC,"Direcciones 0x40 (U8), 0x41 (U12), 0x44 (U13), 0x45 (U14) por A1/A0 (ina226.pdf Table 6-2)."
U10,ADS1115IDGS,Package_SO:TSSOP-10_3x3mm_P0.5mm,1,Texas Instruments,ADS1115IDGSR,C37593,LCSC,"ADC de telemetria, 0x48 (ADDR a GND)."
U11,TMP1075DGK,Package_SO:VSSOP-8_3x3mm_P0.65mm,1,Texas Instruments,TMP1075DGKR,C2864807,LCSC,"Temperatura de placa, 0x49 (A0 a V+)."
U9,ISO1541,Package_SO:SOIC-8_3.9x4.9mm_P1.27mm,1,Texas Instruments,ISO1541DR,C143028,LCSC,Aislador I2C GNDA / GNDD (M1).
U20,LM393B,Package_SO:SOIC-8_3.9x4.9mm_P1.27mm,1,Texas Instruments,LM393BIDR,C2865059,LCSC,"Detector D-F4, colector abierto cableado en OR sobre SHDN_CASCADE."
"U21,U22,U23,U24",TL431BI,Package_TO_SOT_SMD:SOT-23,4,Texas Instruments,TL431BIDBZR,C41283,LCSC,"DBZ: 1 = K, 2 = REF, 3 = A (tl431.pdf Table 5-1). #474 usaba el simbolo TO-92 sobre esta huella."
U25,TL431BI,Package_TO_SOT_SMD:SOT-23,1,Texas Instruments,TL431BIDBZR,C41283,SIN MONTAR,"Sin montar: el disparo del +5 V digital (SCR4), T19 (junta de piezas v5 sec. 4.5). La huella queda en la placa."
"Q3,Q4,Q5",MMBT3906,Package_TO_SOT_SMD:SOT-23,3,onsemi,MMBT3906LT1G,C53444,LCSC,Excitador de puerta de los crowbar D-F6 (TL431 -> PNP -> SCR).
Q6,MMBT3906,Package_TO_SOT_SMD:SOT-23,1,onsemi,MMBT3906LT1G,C53444,SIN MONTAR,"Sin montar: el disparo del +5 V digital (SCR4), T19 (junta de piezas v5 sec. 4.5). La huella queda en la placa."
"SCR1,SCR2,SCR3",BT151-500R,Package_TO_SOT_THT:TO-220-3_Vertical,3,WeEn,"BT151-500R,127",C9211,LCSC,"Tiristor de crowbar D-F6. 1 = K, 2 = A, 3 = G (nxp-bt151-500r.pdf p. 2)."
SCR4,BT151-500R,Package_TO_SOT_THT:TO-220-3_Vertical,1,WeEn,"BT151-500R,127",C9211,SIN MONTAR,"Sin montar: el disparo del +5 V digital (SCR4), T19 (junta de piezas v5 sec. 4.5). La huella queda en la placa."
PS1,THN 30-2422WI,Converter_DCDC:Converter_DCDC_TRACO_THL30-xxxxWI_THT,1,TRACO,THN 30-2422WI,,Farnell/Mouser,"+-12 V de rack, 30 W. Pinout 1x1 pulgada estandar TRACO (traco_thn30wi.pdf p. 5). LCSC lo lista (C6553108) sin stock."
"PS4,PS5",THN 20-2413WI,Converter_DCDC:Converter_DCDC_TRACO_THL30-xxxxWI_THT,2,TRACO,THN 20-2413WI,,Farnell/Mouser,+-15.5 V crudos. Trim HACIA ARRIBA con 45.3k de Trim a -Vout (traco_thn15wi_thn20wi_thn30wi_voltage_adjustment.pdf p. 1). LCSC lo lista (C7361463) sin stock.
PS2,URB2405YMD-20WR3,sam17:Converter_DCDC_Mornsun_URB_YMD-20WR3_Horizontal_THT,1,Mornsun,URB2405YMD-20WR3,,Mouser,"+5 V digital aislado M1. 1 Ctrl, 2 GND, 3 Vin, 4 +Vo, 5 Trim, 6 0V (mornsun_urb_ymd20wr3.pdf p. 6). En LCSC solo hay clones de otras marcas con el mismo nombre: no valen."
PS3,THN 20-2411WI,Converter_DCDC:Converter_DCDC_TRACO_THL30-xxxxWI_THT,1,TRACO,THN 20-2411WI,,Farnell/Mouser,"+5 V de rack, aislado (#491): un buck no aislado con la entrada puenteada a la salida ponia 24 V en el riel antes que el crowbar. Mismo 1x1 pulgada que PS4/PS5 (traco_thn20wi.pdf p. 4); Trim y Remote al aire."
NT1,NetTie GND24-GNDA,NetTie:NetTie-2_SMD_Pad2.0mm,1,—,—,,—,"Unica union entre GND24 y GNDA, entre PS5 y PS3. Con los cinco convertidores aislados no lleva corriente de carga. Es cobre: no se compra."
"L2,L3",22uH SRP1265A-220M,sam17:L_Bourns_SRP1265A,2,Bourns,SRP1265A-220M,C2041465,LCSC,"L2: bobina del filtro LC de +15.5 V (#334): 22 uH +-20 %, Isat 12 A, Irms 9 A, DCR 37 mohm max, SRF 6 MHz tip (bourns_srp1265a.pdf p. 1) y curva L-I publicada (p. 3). Con la SRR1260 (Isat 3.7 A) el fallo de 36 V la saturaba antes de que U19 cortara. L3: la misma pieza en el filtro LC de -15.5 V (22 uH, el valor de rizado_budget.py), una sola referencia en la placa; su huella pasa de 12.5 x 12.5 a 13.5 x 12.5 mm (junta de piezas v5 sec. 4.6)."
"C1,C2",220uF 35V,Capacitor_SMD:CP_Elec_8x10,2,Panasonic,EEEFK1V221P,C178562,LCSC,"Cd de la rama de amortiguamiento (Rd = 0.68 ohm + Cd = 220 uF, rizado_budget.py)."
"C3,C4",47uF 35V,Capacitor_SMD:CP_Elec_6.3x7.7,2,Lelon,VZH470M1VTR-0607,C249923,LCSC,"C principal del filtro LC (47 uF, rizado_budget.py y el modelo RK4 de check_absmax.py)."
"C17,C18",47uF 35V,Capacitor_SMD:CP_Elec_6.3x7.7,2,Lelon,VZH470M1VTR-0607,C249923,LCSC,"Salida de U1/U2: 47 uF electrolitico declarado en margen_budget.py (COUT_U1_F, ESR 0.3 ohm dentro de 0..3 ohm)."
C14,100uF 50V,Capacitor_SMD:CP_Elec_8x10,1,Panasonic,EEEFK1H101P,C178548,LCSC,"Cin del URB2405 (mornsun_urb_ymd20wr3.pdf p. 4, Fig. 2: 100 uF/50 V)."
C29,100uF 25V,Capacitor_SMD:CP_Elec_6.3x7.7,1,Nichicon,UCD1E101MCL1GS,C250945,LCSC,"Cout del URB2405 (p. 4, Fig. 2: 100 uF/16 V)."
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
